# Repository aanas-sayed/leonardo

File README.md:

# Arduino Leonardo - KiCad 8 Port

This project is a fork of the original [Arduino Leonardo KiCad project](https://github.com/eltorio/leonardo). It has been modified to remove any branding restrictions, making it suitable for use in general projects without concerns about licenses or rebuilding the Bill of Materials (BOM). Footprints have been updated to use components from the KiCad standard library, allowing for the use of some of the cheapest products available on the market. These changes ensure a low-cost BOM. 

> [!NOTE] 
> This repository may not be maintained regularly. I am only doing this for a one-off project, but leaving it here in case it benefits anyone else.

## Overview

The Arduino Leonardo board design has been ported to **KiCad 8**, enabling hobbyists and developers to integrate it into their own projects easily.

## Schematic
  
View the full [schematic PDF](https://github.com/eltorio/leonardo/raw/main/schematic.pdf).

## PCB Layout
  
The board layout matches the Arduino Leonardo Rev3 design.

- Default silkscreen **hides component references** for compatibility with Leonardo boards.
- Use the [Hide References Plugin](https://github.com/joelsa/kicad-hide-references-plugin) to toggle component visibility.

## 3D Renders
### Without Component References  

### With Component References  

## Bill of Materials (BOM)
The project includes a detailed, ready-to-use BOM: [View BOM](https://raw.githubusercontent.com/eltorio/leonardo/main/Leonardo_Rev3e.html).

Key details:
- All parts are readily available.
- Includes part numbers for ordering components from Digi-Key.

## License
This project is licensed under the **Attribution-ShareAlike 4.0 International** ([CC BY-SA 4.0](https://creativecommons.org/licenses/by-sa/4.0/)).  
The original design was ported to Kicad by [eltorio](https://github.com/eltorio/leonardo).

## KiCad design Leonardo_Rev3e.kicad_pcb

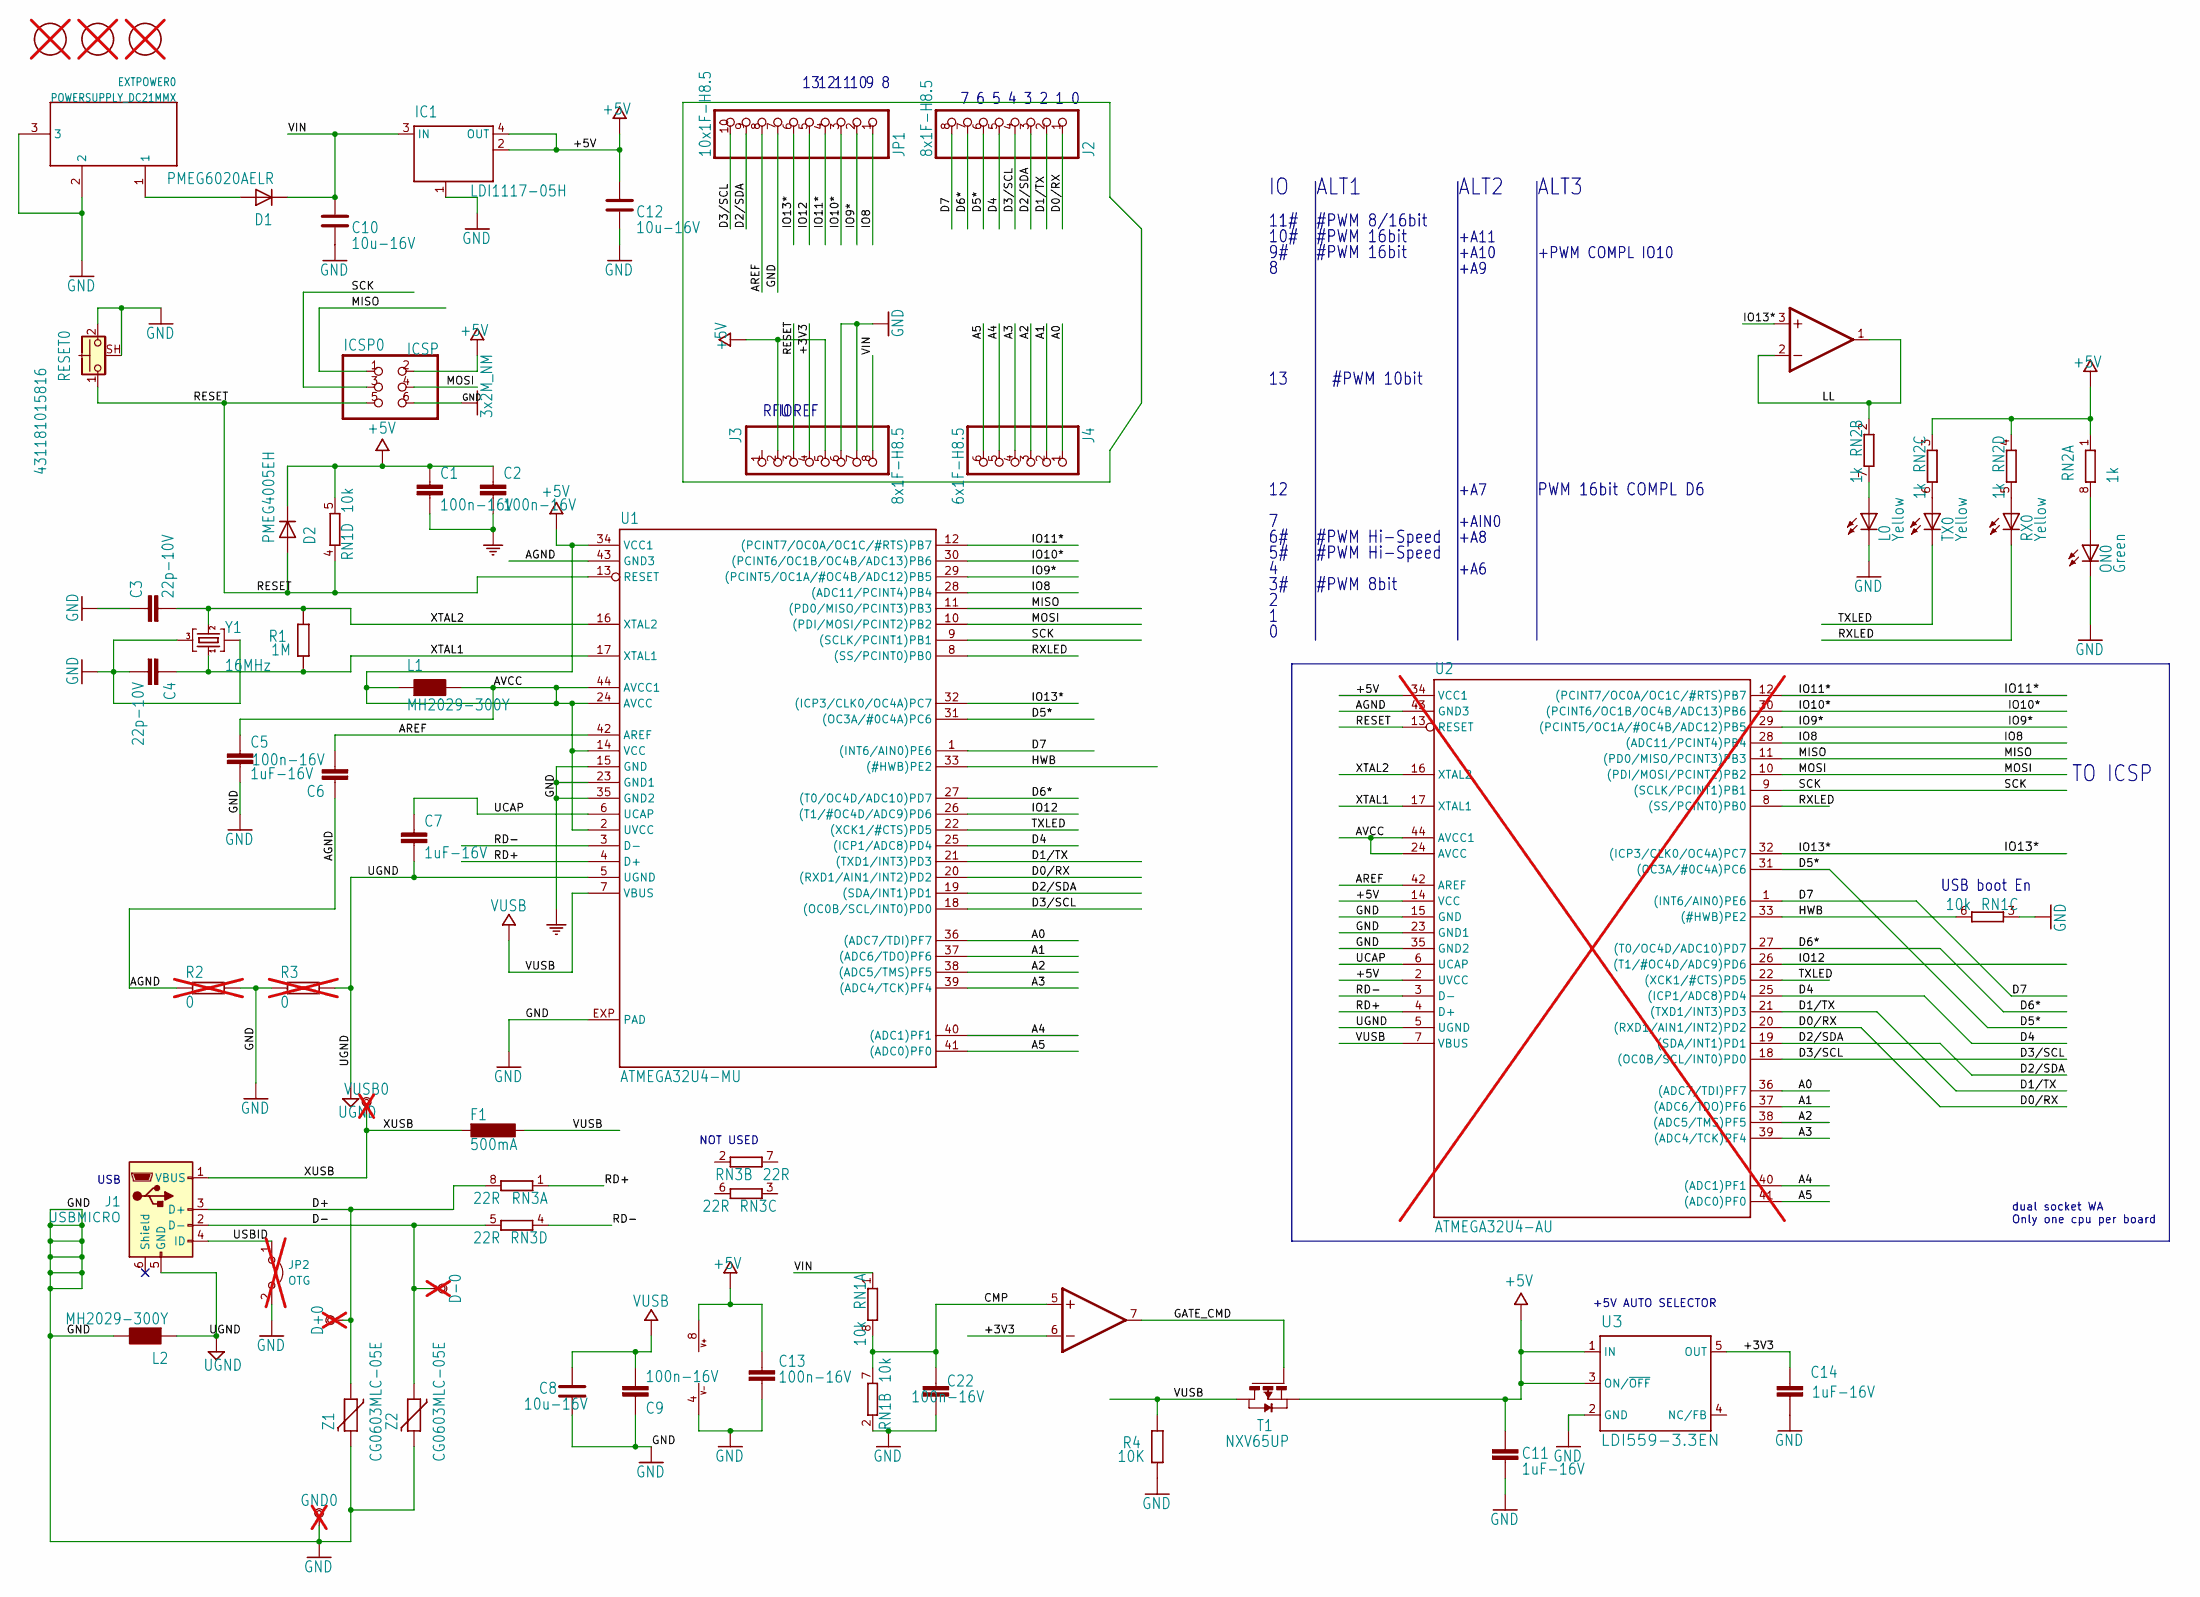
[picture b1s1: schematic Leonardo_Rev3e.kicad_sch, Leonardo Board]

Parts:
C1, C2, C6, C9, C13, C22: 100n-16V; C_0603_1608Metric_Pad1.08x0.95mm_HandSolder; Mfg Part No 885012206046
C3, C4: 22p-10V; C_0603_1608Metric_Pad1.08x0.95mm_HandSolder; Mfg Part No 885012006004
C5, C7, C11, C14: 1uF-16V; C_0603_1608Metric_Pad1.08x0.95mm_HandSolder; Mfg Part No 885012206052
C8, C10, C12: 10u-16V; C_1206_3216Metric_Pad1.33x1.80mm_HandSolder; Mfg Part No 885012208041
D1: PMEG6020AELR; Nexperia_CFP3_SOD-123W; Mfg Part No PMEG6020AELRX
D2: PMEG4005EH; D_SOD-123F; Mfg Part No PMEG4005EH,115
D+0: DNP; TP-1.00MM; not fitted
D-0: DNP; TP-1.00MM; not fitted
EXTPOWER0: POWERSUPPLY_DC21MMX; BarrelJack_Horizontal_Wurth_694108301002; Mfg Part No 694108301002
F1: 500mA; Fuse_1812_4532Metric_Pad1.30x3.40mm_HandSolder; Mfg Part No 0ZCG0050FF2C
FID1, FID2, FID3: DNP; FD-1-1.5; not fitted
GND0: DNP; TP-1.00MM; not fitted
IC1: LDI1117-05H; SOT-223; Mfg Part No LDI1117-05H
IC2: LM358LVIDGKR; MSOP-8_3x3mm_P0.65mm; Mfg Part No LM358LVIDGKR
ICSP0: ICSP; 2X03; Mfg Part No 61300621121
J1: USBMICRO; Micro_USB_2.0_SMT_Type_B_Wurth_629105150521; Mfg Part No 629105150521
J2, J3: 8x1F-H8.5; 1X08; Mfg Part No 61300811821
J4: 6x1F-H8.5; 1X06; Mfg Part No 61300611821
JP1: 10x1F-H8.5; 1X10; Mfg Part No 61301011821
JP2: OTG; HEADER_2_2.54; Mfg Part No 61300211121; not fitted
L0: Yellow; CHIPLED_0805; Mfg Part No 150080YS75000
L1, L2: MH2029-300Y; R_0805_2012Metric_Pad1.20x1.40mm_HandSolder; Mfg Part No 74279206
ON0: Green; CHIPLED_0805; Mfg Part No 150080GS75000
R1: 1M; R_0603_1608Metric_Pad0.98x0.95mm_HandSolder; Mfg Part No CR0603-FX-1004ELF
R2, R3: 0; R_0402_1005Metric_Pad0.72x0.64mm_HandSolder; Mfg Part No RC0603FR-070RL; not fitted
R4: 10K; R_0603_1608Metric_Pad0.98x0.95mm_HandSolder; Mfg Part No RMC1/16-103JTP
RESET0: 431181015816; PushButton_Wurth_431181015816; Mfg Part No 431181015816
RN1: 10k; R_Cat16-4; Mfg Part No CAY16-1002F4LF
RN2: 1k; R_Cat16-4; Mfg Part No CAY16-1001F4LF
RN3: 22R; R_Cat16-4; Mfg Part No CAY16-22R0F4LF
RX0: Yellow; CHIPLED_0805; Mfg Part No 150080YS75000
T1: NXV65UP; SOT-23; Mfg Part No NXV65UPR
TX0: Yellow; CHIPLED_0805; Mfg Part No 150080YS75000
U1: ATMEGA32U4-MU; QFN44ML7X7; Mfg Part No ATMEGA32U4-MU
U2: ATMEGA32U4-AU; TQFP44-PAD; Mfg Part No ATMEGA32U4-AU; not fitted
U3: LDI559-3.3EN; SOT-23-5; Mfg Part No LDI559-3.3EN
VUSB0: DNP; TP-1.00MM; not fitted
Y1: 16MHz; CRYSTAL-3.2-2.5; Mfg Part No 12.88722
Z1, Z2: CG0603MLC-05E; R_0603_1608Metric_Pad0.98x0.95mm_HandSolder; Mfg Part No 82306050029

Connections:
3x2M_NM: C1.2, C2.2, C3.1, C4.2, C5.2, C8.2, C9.1, C10.2, C11.1, C12.2, C13.2, C14.1, C22.1, EXTPOWER0.2, EXTPOWER0.3, GND0.X, IC1.1 (GND/ADJ), IC2.4 (V-), ICSP0.6, J3.6, J3.7, JP1.7, JP2.2 (B), L0.C, L2.2, ON0.C, R2.2, R3.1, R4.1, RESET0.2, RESET0.SH (B), RN1.2 (1), RN1.3 (1), U1.15 (GND), U1.23 (GND1), U1.35 (GND2), U1.EXP (PAD), U2.15 (GND), U2.23 (GND1), U2.35 (GND2), U3.2 (GND), Y1.2 (GND@1), Y1.4 (GND@2), Z1.2, Z2.2
+5V: C1.1, C2.1, C5.1, C11.2, C12.1, C13.1, D2.1 (K), IC1.2 (OUT@1), IC1.4 (OUT), IC2.8 (V+), ICSP0.2, J3.2, J3.5, L1.1, L1.2, RN1.5 (2), RN2.1, RN2.3 (1), RN2.4 (1), T1.2 (S), U1.2 (UVCC), U1.14 (VCC), U1.24 (AVCC), U1.34 (VCC1), U1.44 (AVCC1), U2.2 (UVCC), U2.14 (VCC), U2.24 (AVCC), U2.34 (VCC1), U2.44 (AVCC1), U3.1 (IN), U3.3 (ON/~OFF)
/+3V3: C14.2, IC2.6 (-IN), J3.4, U3.5 (OUT)
/A0: J4.1, U1.36 ((ADC7/TDI)PF7), U2.36 ((ADC7/TDI)PF7)
/A1: J4.2, U1.37 ((ADC6/TDO)PF6), U2.37 ((ADC6/TDO)PF6)
/A2: J4.3, U1.38 ((ADC5/TMS)PF5), U2.38 ((ADC5/TMS)PF5)
/A3: J4.4, U1.39 ((ADC4/TCK)PF4), U2.39 ((ADC4/TCK)PF4)
/A4: J4.5, U1.40 ((ADC1)PF1), U2.40 ((ADC1)PF1)
/A5: J4.6, U1.41 ((ADC0)PF0), U2.41 ((ADC0)PF0)
/AGND: C6.1, R2.1, U1.43 (GND3), U2.43 (GND3)
/AREF: C6.2, JP1.8, U1.42 (AREF), U2.42 (AREF)
/CMP: C22.2, IC2.5 (+IN), RN1.7 (2), RN1.8 (2)
/D0/RX: J2.1, U1.20 ((RXD1/AIN1/INT2)PD2), U2.20 ((RXD1/AIN1/INT2)PD2)
/D1/TX: J2.2, U1.21 ((TXD1/INT3)PD3), U2.21 ((TXD1/INT3)PD3)
/D2/SDA: J2.3, JP1.9, U1.19 ((SDA/INT1)PD1), U2.19 ((SDA/INT1)PD1)
/D3/SCL: J2.4, JP1.10, U1.18 ((OC0B/SCL/INT0)PD0), U2.18 ((OC0B/SCL/INT0)PD0)
/D4: J2.5, U1.25 ((ICP1/ADC8)PD4), U2.25 ((ICP1/ADC8)PD4)
/D5*: J2.6, U1.31 ((OC3A/#0C4A)PC6), U2.31 ((OC3A/#0C4A)PC6)
/D6*: J2.7, U1.27 ((T0/OC4D/ADC10)PD7), U2.27 ((T0/OC4D/ADC10)PD7)
/D7: J2.8, U1.1 ((INT6/AIN0)PE6), U2.1 ((INT6/AIN0)PE6)
/D+: D+0.X, J1.3 (D+), RN3.8 (2), Z1.1
/D-: D-0.X, J1.2 (D-), RN3.5 (2), Z2.1
/GATE_CMD: IC2.7 (OUT), T1.1 (G)
/HWB: RN1.6 (2), U1.33 ((#HWB)PE2), U2.33 ((#HWB)PE2)
/IO8: JP1.1, U1.28 ((ADC11/PCINT4)PB4), U2.28 ((ADC11/PCINT4)PB4)
/IO9*: JP1.2, U1.29 ((PCINT5/OC1A/#OC4B/ADC12)PB5), U2.29 ((PCINT5/OC1A/#OC4B/ADC12)PB5)
/IO10*: JP1.3, U1.30 ((PCINT6/OC1B/OC4B/ADC13)PB6), U2.30 ((PCINT6/OC1B/OC4B/ADC13)PB6)
/IO11*: JP1.4, U1.12 ((PCINT7/OC0A/OC1C/#RTS)PB7), U2.12 ((PCINT7/OC0A/OC1C/#RTS)PB7)
/IO12: JP1.5, U1.26 ((T1/#OC4D/ADC9)PD6), U2.26 ((T1/#OC4D/ADC9)PD6)
/IO13*: IC2.3 (+IN), JP1.6, U1.32 ((ICP3/CLK0/OC4A)PC7), U2.32 ((ICP3/CLK0/OC4A)PC7)
/LL: IC2.1 (OUT), IC2.2 (-IN), RN2.2 (1)
/MISO: ICSP0.1, U1.11 ((PD0/MISO/PCINT3)PB3), U2.11 ((PD0/MISO/PCINT3)PB3)
/MOSI: ICSP0.4, U1.10 ((PDI/MOSI/PCINT2)PB2), U2.10 ((PDI/MOSI/PCINT2)PB2)
/RD+: RN3.1, U1.4 (D+), U2.4 (D+)
/RD-: RN3.4 (1), U1.3 (D-), U2.3 (D-)
/RESET: D2.2 (A), ICSP0.5, J3.3, RESET0.1, RN1.4 (1), U1.13 (RESET), U2.13 (RESET)
/RXLED: RX0.C, U1.8 ((SS/PCINT0)PB0), U2.8 ((SS/PCINT0)PB0)
/SCK: ICSP0.3, U1.9 ((SCLK/PCINT1)PB1), U2.9 ((SCLK/PCINT1)PB1)
/TXLED: TX0.C, U1.22 ((XCK1/#CTS)PD5), U2.22 ((XCK1/#CTS)PD5)
/UCAP: C7.1, U1.6 (UCAP), U2.6 (UCAP)
/USBID: J1.4 (ID), JP2.1 (A)
/VIN: C10.1, D1.1 (K), IC1.3 (IN), J3.8, RN1.1
/XTAL1: C4.1, R1.1, U1.17 (XTAL1), U2.17 (XTAL1), Y1.1 (C1)
/XTAL2: C3.2, R1.2, U1.16 (XTAL2), U2.16 (XTAL2), Y1.3 (C2)
/XUSB: F1.2, J1.1 (VBUS), VUSB0.X
unnamed: D1.2 (A), EXTPOWER0.1
unnamed: ON0.A, RN2.8 (2)
unnamed: L0.A, RN2.7 (2)
unnamed: RN2.6 (2), TX0.A
unnamed: RN2.5 (2), RX0.A
UGND: C7.2, J1.5 (GND), L2.1, R3.2, U1.5 (UGND), U2.5 (UGND)
VUSB: C8.1, C9.2, F1.1, R4.2, T1.3 (D), U1.7 (VBUS), U2.7 (VBUS)

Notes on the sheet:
#PWM 8/16bit
PWM 16bit COMPL D6
USB boot En
NOT USED
RFU
#PWM 8bit
+PWM COMPL IO10
#PWM 16bit
TO ICSP
dual socket WA Only one cpu per board
#PWM Hi-Speed
+A10
11#
IOREF
+5V AUTO SELECTOR
+AIN0
ALT3
+A8
+A9
ALT1
+A6
#PWM 10bit
USB
ALT2
10#
+A11
+A7

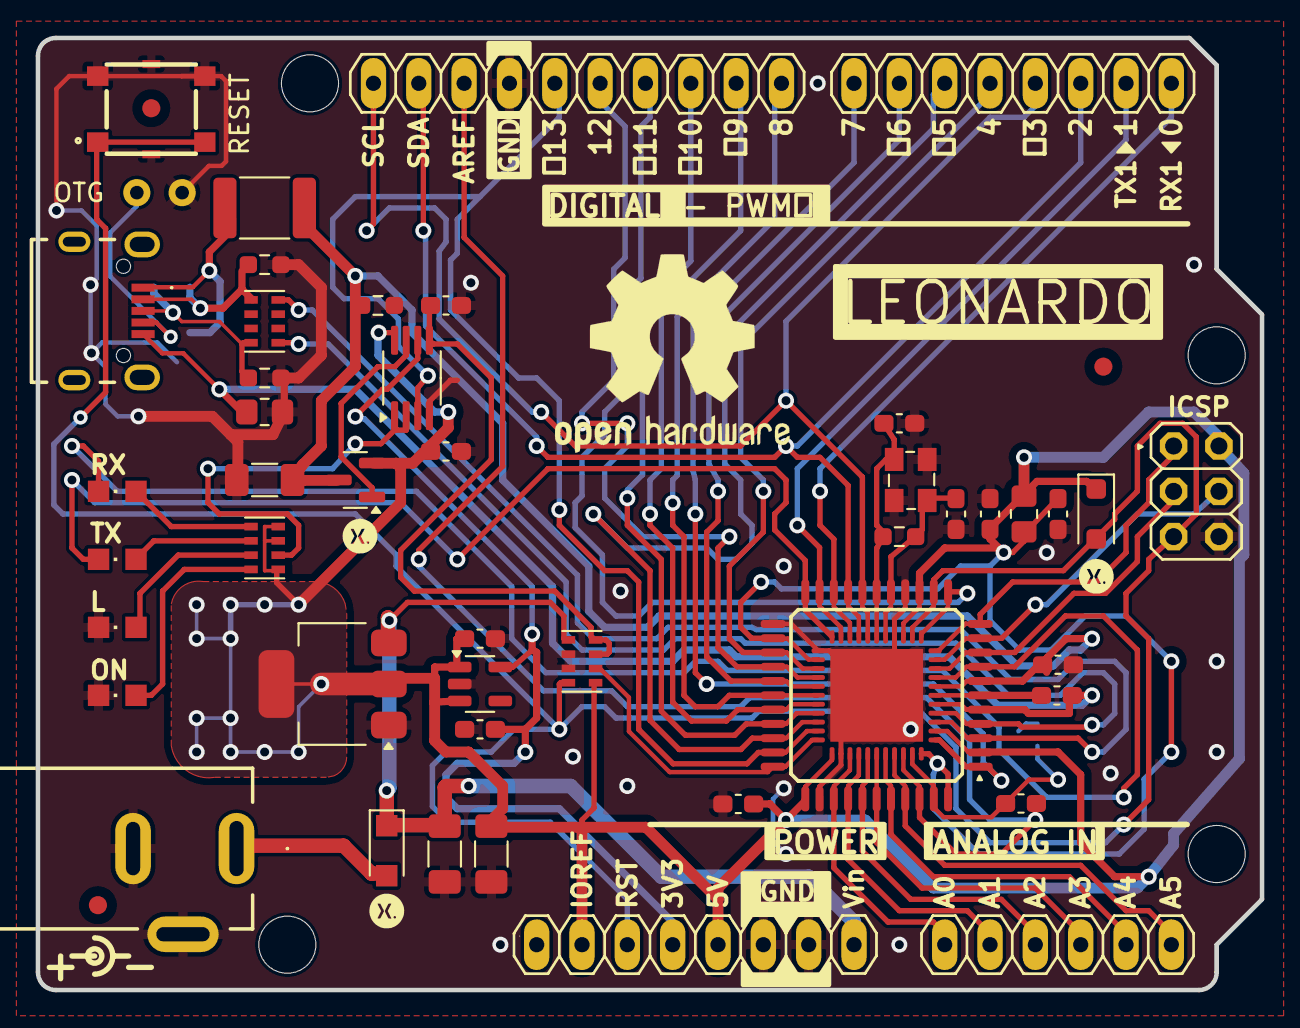
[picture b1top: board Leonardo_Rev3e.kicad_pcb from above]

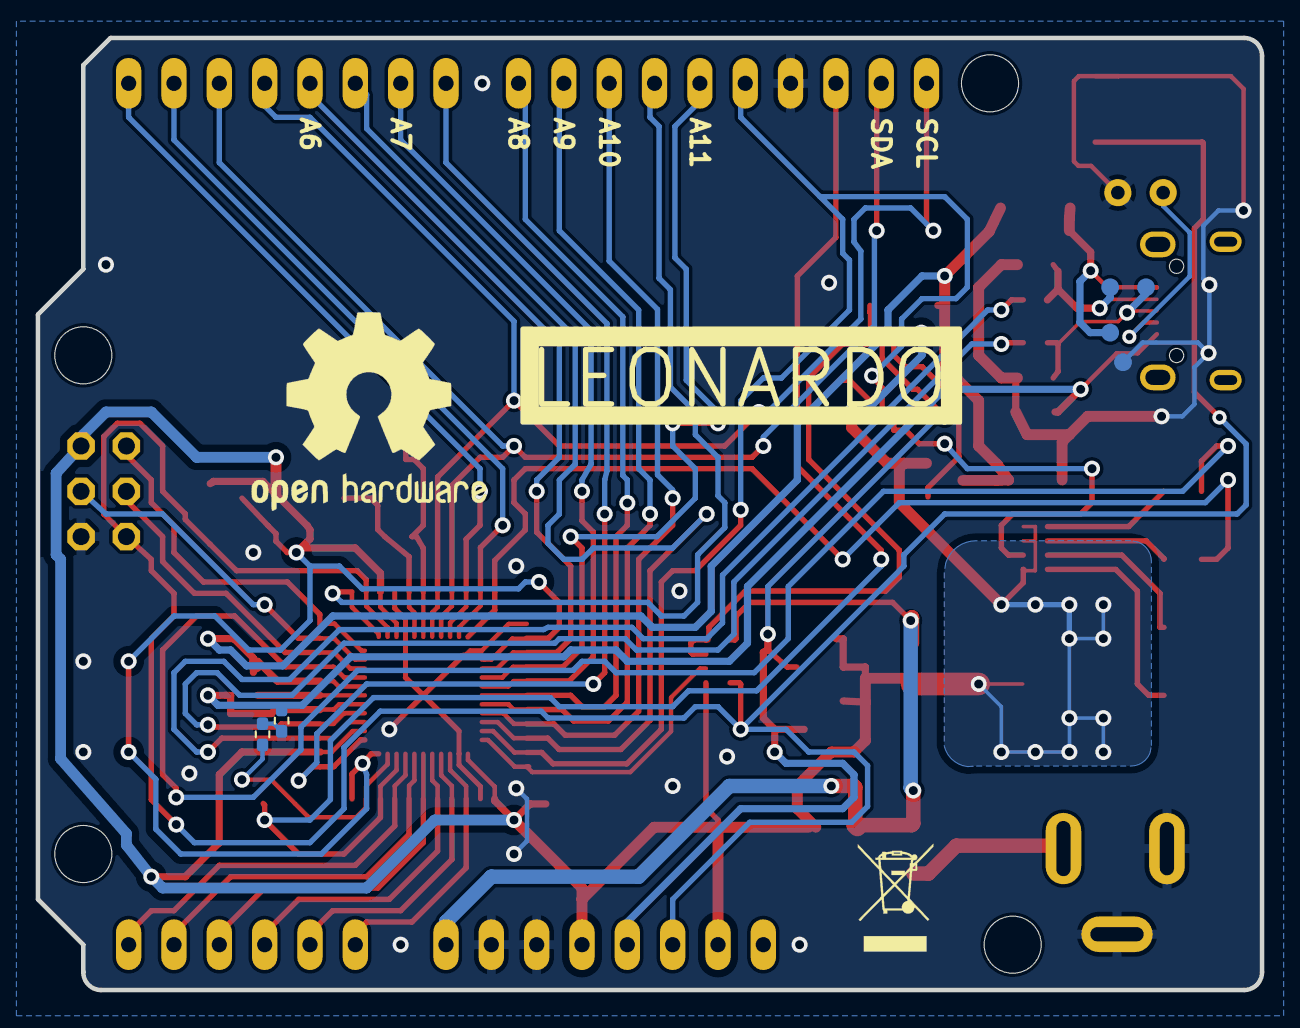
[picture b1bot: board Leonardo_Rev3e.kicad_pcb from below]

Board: 2 copper layers, 68.6 x 53.3 mm, 60 parts (3 on the bottom side), 52 nets.

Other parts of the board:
@HOLE0, @HOLE1, @HOLE2, @HOLE3: (no value)

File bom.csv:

"Reference","Value","Datasheet","Footprint","Qty","DNP","Vendor Part No","Manufacturer","Mfg Part No","Vendor"
"C1,C2,C6,C9,C13,C22","100n-16V","https://www.we-online.com/components/products/datasheet/8850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","Capacitor_SMD:C_0603_1608Metric_Pad1.08x0.95mm_HandSolder","6","","710-885012206046","WURTH ELEKTRONIK ","885012206046","MOUSER"
"C3,C4","22p-10V","https://www.we-online.com/components/products/datasheet/8850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","Capacitor_SMD:C_0603_1608Metric_Pad1.08x0.95mm_HandSolder","2","","710-885012006004","WURTH ELEKTRONIK ","885012006004","MOUSER"
"C5,C7,C11,C14","1uF-16V","https://www.we-online.com/components/products/datasheet/8850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","Capacitor_SMD:C_0603_1608Metric_Pad1.08x0.95mm_HandSolder","4","","710-885012206052","WURTH ELEKTRONIK ","885012206052","MOUSER"
"C8,C10,C12","10u-16V","https://www.we-online.com/components/products/datasheet/8850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","Capacitor_SMD:C_1206_3216Metric_Pad1.33x1.80mm_HandSolder","3","","710-885012208041","WURTH ELEKTRONIK ","885012208041","MOUSER"
"D1","PMEG6020AELR","https://assets.nexperia.com/documents/data-sheet/PMEG6020AELR.pdf","Diode_SMD:Nexperia_CFP3_SOD-123W","1","","771-PMEG6020AELRX","NEXPERIA","PMEG6020AELRX","MOUSER"
"D2","PMEG4005EH","https://assets.nexperia.com/documents/data-sheet/PMEG4005EH.pdf","Diode_SMD:D_SOD-123F","1","","771-PMEG4005EH-T/R","NEXPERIA","PMEG4005EH,115","MOUSER"
"EXTPOWER0","POWERSUPPLY_DC21MMX","https://www.we-online.com/components/products/datasheet/6941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","Leonardo_Rev3e:BarrelJack_Horizontal_Wurth_694108301002","1","","710-694108301002","WURTH ELEKTRONIK ","694108301002","MOUSER"
"F1","500mA","https://www.belfuse.com/resources/datasheets/circuitprotecti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","Fuse:Fuse_1812_4532Metric_Pad1.30x3.40mm_HandSolder","1","","530-0ZCG0050FF2C","BEL FUSE","0ZCG0050FF2C","MOUSER"
"IC1","LDI1117-05H","https://diotec.com/request/datasheet/ldi1117h.pdf","Package_TO_SOT_SMD:SOT-223","1","","637-LDI1117-05H","DIOTEC SEMICONDUCTOR","LDI1117-05H","MOUSER"
"IC2","LM358LVIDGKR","https://www.ti.com/lit/ds/symlink/lm358lv.pdf","Package_SO:MSOP-8_3x3mm_P0.65mm","1","","595-LM358LVIDGKR","TEXAS INSTRUMENTS","LM358LVIDGKR","MOUSER"
"ICSP0","ICSP","https://www.we-online.com/components/products/datasheet/6130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","Leonardo_Rev3e:2X03","1","","710-61300621121","WURTH ELEKTRONIK ","61300621121","MOUSER"
"J1","USBMICRO","https://www.we-online.com/components/products/datasheet/6291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","Leonardo_Rev3e:Micro_USB_2.0_SMT_Type_B_Wurth_629105150521","1","","710-629105150521","WURTH ELEKTRONIK ","629105150521","MOUSER"
"J2,J3","8x1F-H8.5","https://www.we-online.com/components/products/datasheet/6130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","Leonardo_Rev3e:1X08","2","","710-61300811821","WURTH ELEKTRONIK ","61300811821","MOUSER"
"J4","6x1F-H8.5","https://www.we-online.com/components/products/datasheet/6130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","Leonardo_Rev3e:1X06","1","","710-61300611821","WURTH ELEKTRONIK ","61300611821","MOUSER"
"JP1","10x1F-H8.5","https://www.we-online.com/components/products/datasheet/6130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","Leonardo_Rev3e:1X10","1","","710-61301011821","WURTH ELEKTRONIK ","61301011821","MOUSER"
"JP2","OTG","https://www.we-online.com/components/products/datasheet/6130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","Leonardo_Rev3e:HEADER_2_2.54","1","DNP","710-61300211121","WURTH ELEKTRONIK ","61300211121","MOUSER"
"L0,RX0,TX0","Yellow","https://www.we-online.com/components/products/datasheet/1500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","Leonardo_Rev3e:CHIPLED_0805","3","","710-150080YS75000","WURTH ELEKTRONIK ","150080YS75000","MOUSER"
"L1,L2","MH2029-300Y","https://www.we-online.com/components/products/datasheet/7427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","Resistor_SMD:R_0805_2012Metric_Pad1.20x1.40mm_HandSolder","2","","710-74279206","WURTH ELEKTRONIK ","74279206","MOUSER"
"ON0","Green","https://www.we-online.com/components/products/datasheet/1500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","Leonardo_Rev3e:CHIPLED_0805","1","","710-150080GS75000","WURTH ELEKTRONIK ","150080GS75000","MOUSER"
"R1","1M","https://www.bourns.com/docs/product-datasheets/cr.pdf?sfvrsn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","Resistor_SMD:R_0603_1608Metric_Pad0.98x0.95mm_HandSolder","1","","652-CR0603FX-1004ELF","BOURNS","CR0603-FX-1004ELF","MOUSER"
"R2,R3","0","https://www.yageo.com/upload/media/product/products/datashee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","Resistor_SMD:R_0402_1005Metric_Pad0.72x0.64mm_HandSolder","2","DNP","603-RC0603FR-070RL","YAGEO","RC0603FR-070RL","MOUSER"
"R4","10K","http://www.kamaya.co.jp/upload/products_pdf/kamaya_products(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,RMC1-20,RMC1-16S,RMC1-16,RMC1-10,RMC1-8,RMC1-4,RMC1-2,RMC1)_english_20240824_132441.pdf","Resistor_SMD:R_0603_1608Metric_Pad0.98x0.95mm_HandSolder","1","","791-RMC1/16103JTP","KAMAYA","RMC1/16-103JTP","MOUSER"
"RESET0","431181015816","https://www.we-online.com/components/products/datasheet/4311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","Leonardo_Rev3e:PushButton_Wurth_431181015816","1","","710-431181015816","WURTH ELEKTRONIK ","431181015816","MOUSER"
"RN1","10k","https://www.bourns.com/data/global/pdfs/CATCAY.pdf","Resistor_SMD:R_Cat16-4","1","","652-CAY16-1002F4LF","BOURNS","CAY16-1002F4LF","MOUSER"
"RN2","1k","https://www.bourns.com/data/global/pdfs/CATCAY.pdf","Resistor_SMD:R_Cat16-4","1","","652-CAY16-1001F4LF","BOURNS","CAY16-1001F4LF","MOUSER"
"RN3","22R","https://www.bourns.com/data/global/pdfs/CATCAY.pdf","Resistor_SMD:R_Cat16-4","1","","652-CAY16-22R0F4LF","BOURNS","CAY16-22R0F4LF","MOUSER"
"T1","NXV65UP","https://assets.nexperia.com/documents/data-sheet/NXV65UP.pdf","Package_TO_SOT_SMD:SOT-23","1","","771-NXV65UPR","NEXPERIA","NXV65UPR","MOUSER"
"U1","ATMEGA32U4-MU","https://ww1.microchip.com/downloads/en/DeviceDoc/Atmel-7766-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","Leonardo_Rev3e:QFN44ML7X7","1","","556-ATMEGA32U4-MU","MICROCHIP TECHNOLOGY","ATMEGA32U4-MU","MOUSER"
"U2","ATMEGA32U4-AU","https://ww1.microchip.com/downloads/en/DeviceDoc/Atmel-7766-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","Leonardo_Rev3e:TQFP44-PAD","1","DNP","556-ATMEGA32U4-AU","MICROCHIP TECHNOLOGY","ATMEGA32U4-AU","MOUSER"
"U3","LDI559-3.3EN","https://diotec.com/request/datasheet/ldi559en.pdf","Package_TO_SOT_SMD:SOT-23-5","1","","637-LDI559-3.3EN","DIOTEC SEMICONDUCTOR","LDI559-3.3EN","MOUSER"
"Y1","16MHz","https://www.geyer-electronic.shop/downloads/products/1288722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","Leonardo_Rev3e:CRYSTAL-3.2-2.5","1","","4983-12.88722CT-ND","GEYER ELECTRONIC AMERICA, INC.","12.88722","DIGIKEY"
"Z1,Z2","CG0603MLC-05E","https://www.we-online.com/components/products/datasheet/8230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","Resistor_SMD:R_0603_1608Metric_Pad0.98x0.95mm_HandSolder","2","","710-82306050029","WURTH ELEKTRONIK ","82306050029","MOUSER"

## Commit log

2024-12-17 chore: adapt for forked repo
2024-12-23 chore: clean up footprints
2024-12-23 chore: update .gitignore
2025-01-06 feat: use def. sym/foot and customised BOM and silkscreen
2025-01-06 chore: add exported bom
2025-01-06 chore: update bom
2025-01-06 chore: update schematic export
2025-01-07 chore: sort bom columns
2025-01-07 chore: remove trailing whitespaces in BOM

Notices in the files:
Leonardo_Rev3e.kicad_pcb:
Arduino © Leonardo (https://content.arduino.cc/assets/Leonardo-reference.zip)
parts and their libraries:
©Arduino s.r.l / Ronan LE MEILLAT
